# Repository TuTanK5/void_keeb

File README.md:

# void_keeb
My take at a split 56 key keeb.

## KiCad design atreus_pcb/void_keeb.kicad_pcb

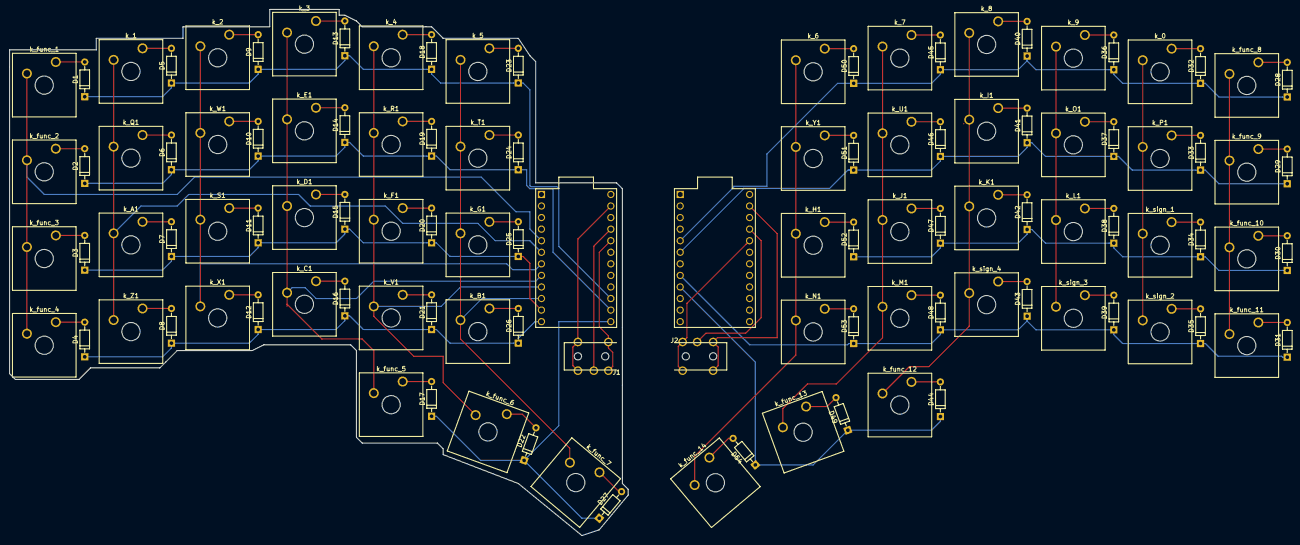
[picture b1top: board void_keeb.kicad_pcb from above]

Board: 2 copper layers, 135.9 x 115.6 mm, 112 parts (0 on the bottom side), 82 nets.

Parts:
D1, D2, D3, D4, D5, D6, D7, D8, D9, D10, D11, D12, D13, D14, D15, D16, D17, D18, D19, D20, D21, D22, D23, D24, D25, D26, D27, D28, D29, D30, D31, D32, D33, D34, D35, D36, D37, D38, D39, D40, D41, D42, D43, D44, D45, D46, D47, D48, D49, D50, D51, D52, D53, D54: 1N4148; D_DO-35_SOD27_P7.62mm_Horizontal
J1, J2: AudioJack3_Ground; PJ-313-TH_mod
U1, U2: ProMicro
k_0, k_1, k_2, k_3, k_4, k_5, k_6, k_7, k_8, k_9: SW_Push; SW_Cherry_MX1A_1.00u_Plate
k_A1: SW_Push; SW_Cherry_MX1A_1.00u_Plate
k_B1: SW_Push; SW_Cherry_MX1A_1.00u_Plate
k_C1: SW_Push; SW_Cherry_MX1A_1.00u_Plate
k_D1: SW_Push; SW_Cherry_MX1A_1.00u_Plate
k_E1: SW_Push; SW_Cherry_MX1A_1.00u_Plate
k_F1: SW_Push; SW_Cherry_MX1A_1.00u_Plate
k_G1: SW_Push; SW_Cherry_MX1A_1.00u_Plate
k_H1: SW_Push; SW_Cherry_MX1A_1.00u_Plate
k_I1: SW_Push; SW_Cherry_MX1A_1.00u_Plate
k_J1: SW_Push; SW_Cherry_MX1A_1.00u_Plate
k_K1: SW_Push; SW_Cherry_MX1A_1.00u_Plate
k_L1: SW_Push; SW_Cherry_MX1A_1.00u_Plate
k_M1: SW_Push; SW_Cherry_MX1A_1.00u_Plate
k_N1: SW_Push; SW_Cherry_MX1A_1.00u_Plate
k_O1: SW_Push; SW_Cherry_MX1A_1.00u_Plate
k_P1: SW_Push; SW_Cherry_MX1A_1.00u_Plate
k_Q1: SW_Push; SW_Cherry_MX1A_1.00u_Plate
k_R1: SW_Push; SW_Cherry_MX1A_1.00u_Plate
k_S1: SW_Push; SW_Cherry_MX1A_1.00u_Plate
k_T1: SW_Push; SW_Cherry_MX1A_1.00u_Plate
k_U1: SW_Push; SW_Cherry_MX1A_1.00u_Plate
k_V1: SW_Push; SW_Cherry_MX1A_1.00u_Plate
k_W1: SW_Push; SW_Cherry_MX1A_1.00u_Plate
k_X1: SW_Push; SW_Cherry_MX1A_1.00u_Plate
k_Y1: SW_Push; SW_Cherry_MX1A_1.00u_Plate
k_Z1: SW_Push; SW_Cherry_MX1A_1.00u_Plate
k_func_1, k_func_2, k_func_3, k_func_4, k_func_5, k_func_6, k_func_7, k_func_8, k_func_9, k_func_10, k_func_11, k_func_12, k_func_13, k_func_14: SW_Push; SW_Cherry_MX1A_1.00u_Plate
k_sign_1, k_sign_2, k_sign_3, k_sign_4: SW_Push; SW_Cherry_MX1A_1.00u_Plate

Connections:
unnamed: D1.1, D5.1, D9.1, D13.1, D18.1, D23.1, U1.15
unnamed: D1.2, k_func_1.1
unnamed: D2.2, k_func_2.1
unnamed: D3.2, k_func_3.1
unnamed: D4.2, k_func_4.1
unnamed: D5.2, k_1.1
unnamed: D6.2, k_Q1.1
unnamed: D7.2, k_A1.1
unnamed: D8.2, k_Z1.1
unnamed: D9.2, k_2.1
unnamed: D2.1, D6.1, D10.1, D14.1, D19.1, D24.1, U1.14
unnamed: D10.2, k_W1.1
unnamed: D3.1, D7.1, D11.1, D15.1, D20.1, D25.1, U1.11
unnamed: D11.2, k_S1.1
unnamed: D4.1, D8.1, D12.1, D16.1, D21.1, D26.1, U1.12
unnamed: D12.2, k_X1.1
unnamed: D13.2, k_3.1
unnamed: D14.2, k_E1.1
unnamed: D15.2, k_D1.1
unnamed: D16.2, k_C1.1
unnamed: D17.1, D22.1, D27.1, U1.13
unnamed: D17.2, k_func_5.1
unnamed: D18.2, k_4.1
unnamed: D19.2, k_R1.1
unnamed: D20.2, k_F1.1
unnamed: D21.2, k_V1.1
unnamed: D22.2, k_func_6.1
unnamed: D23.2, k_5.1
unnamed: D24.2, k_T1.1
unnamed: D25.2, k_G1.1
unnamed: D26.2, k_B1.1
unnamed: D27.2, k_func_7.1
unnamed: D28.1, D32.1, D36.1, D40.1, D45.1, D50.1, U2.5
unnamed: D28.2, k_func_8.1
unnamed: D29.1, D33.1, D37.1, D41.1, D46.1, D51.1, U2.6
unnamed: D29.2, k_func_9.1
unnamed: D30.1, D34.1, D38.1, D42.1, D47.1, D52.1, U2.7
unnamed: D30.2, k_func_10.1
unnamed: D31.1, D35.1, D39.1, D43.1, D48.1, D53.1, U2.8
unnamed: D31.2, k_func_11.1
unnamed: D32.2, k_0.1
unnamed: D33.2, k_P1.1
unnamed: D34.2, k_sign_1.1
unnamed: D35.2, k_sign_2.1
unnamed: D36.2, k_9.1
unnamed: D37.2, k_O1.1
unnamed: D38.2, k_L1.1
unnamed: D39.2, k_sign_3.1
unnamed: D40.2, k_8.1
unnamed: D41.2, k_I1.1
unnamed: D42.2, k_K1.1
unnamed: D43.2, k_sign_4.1
unnamed: D44.1, D49.1, D54.1, U2.9
unnamed: D44.2, k_func_12.1
unnamed: D45.2, k_7.1
unnamed: D46.2, k_U1.1
unnamed: D47.2, k_J1.1
unnamed: D48.2, k_M1.1
unnamed: D49.2, k_func_13.1
unnamed: D50.2, k_6.1
unnamed: D51.2, k_Y1.1
unnamed: D52.2, k_H1.1
unnamed: D53.2, k_N1.1
unnamed: D54.2, k_func_14.1
unnamed: J1.R, U1.21
unnamed: J1.S, U1.20
unnamed: J1.T, U1.23
unnamed: J2.R, U2.21
unnamed: J2.S, U2.20
unnamed: J2.T, U2.23
unnamed: U1.5, k_func_1.2, k_func_2.2, k_func_3.2, k_func_4.2
unnamed: U1.6, k_1.2, k_A1.2, k_Q1.2, k_Z1.2
unnamed: U1.7, k_2.2, k_S1.2, k_W1.2, k_X1.2
unnamed: U1.8, k_3.2, k_C1.2, k_D1.2, k_E1.2, k_func_5.2
unnamed: U1.9, k_4.2, k_F1.2, k_R1.2, k_V1.2, k_func_6.2
unnamed: U1.10, k_5.2, k_B1.2, k_G1.2, k_T1.2, k_func_7.2
unnamed: U2.11, k_6.2, k_H1.2, k_N1.2, k_Y1.2, k_func_14.2
unnamed: U2.12, k_7.2, k_J1.2, k_M1.2, k_U1.2, k_func_13.2
unnamed: U2.16, k_func_8.2, k_func_9.2, k_func_10.2, k_func_11.2
unnamed: U2.17, k_0.2, k_P1.2, k_sign_1.2, k_sign_2.2
unnamed: U2.18, k_9.2, k_L1.2, k_O1.2, k_sign_3.2
unnamed: U2.19, k_8.2, k_I1.2, k_K1.2, k_func_12.2, k_sign_4.2

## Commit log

2018-10-05 Schematic
2018-10-08 ignore
2018-10-10 Initial readme
2018-10-24 Create LICENSE
2018-10-24 Restructure and add submodules
2018-10-24 Update mitosis-hardware
